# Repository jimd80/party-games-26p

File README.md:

# 26 Player party game setup

Up to 26 senders

go to a single receiver

Sending keys A–Z for 26 players.

## The concept
Up to 26 micro:bits act as wireless game controllers. One micro:bit is used as a receiver. Each time a player presses a button, the receiver micro:bit sends a character (A–Z) to the serial port of the Arduino. The Arduino acts as a virtual keyboard for the PC and passes the player's keystrokes as a–z keypresses (player 1 = a, player 2 = b, ..., player 26 = z).

This has some benefits:
- No drivers required; works on any PC, Mac, Chromebook, tablet, etc.
- Games can be developed without the hardware; just use the keyboard `a`–`z` keys to test!
- Easy to develop!

## Setup
Of course you'll need games to play. Check out [games-examples](games-examples/README.md) for a guide on how to write games or directly try the examples.

### The sender
For the sender you have 2 options:
- A micro:bit with a battery box
- Or build the [game controller](https://github.com/jimd80/pxt-coderdojo-controller)

Load [microbit-GameController-v25.12.hex](sender-microbit-src/microbit-GameController-v25.12.hex) from [sender-microbit-src](sender-microbit-src/README.md) into each sender micro:bit using [MakeCode](https://makecode.microbit.org/#editor) or drag it to the `MICROBIT` folder in your file manager.

### The receiver
Get an Arduino Micro, or the Pro Micro clone. Flash [receiver-arduino-v25.7.hex](receiver-arduino-src/release/receiver-arduino-v25.7.hex) from [receiver-arduino-src](receiver-arduino-src/README.md) into the Arduino.

Get a dedicated micro:bit to use as a receiver. Flash [microbit-GameReceiver-v26.3.hex](receiver-microbit-src/microbit-GameReceiver-v26.3.hex) from [receiver-microbit-src](receiver-microbit-src/README.md) into the receiver micro:bit.

Connect the Arduino and micro:bit with 3 wires, as described in [receiver-arduino-src](receiver-arduino-src/README.md).

Alternatively, build the receiver PCB as described in [receiver-pcb](receiver-pcb/README.md).

## How to play
There are plenty of modes to use this setup. We'll go from easy to advanced.

### Quick 26 player
The easiest and fastest setup to play a multiplayer game.

**Senders**: Players just need to turn on their micro:bit. A `?` will appear shortly and a letter is auto-assigned. Button A is the action key to play.

**Receiver**: Plug in the receiver. `26` will appear briefly on the screen. Press button B until `A` (**A**uto-assign) appears and press button A to confirm.

### Personalized 26 player
The controllers are personalized. Give each player a secret code they need to enter into their micro:bit in order for their predefined letter to appear. If managed well, games can keep a preset list of the players' names to show in-game names of the players. The list of "secret codes" can be found in [sender-microbit-src](sender-microbit-src/README.md).

**Senders**: After a player has powered up their micro:bit, a `?` will appear. Now they need to input their code by pressing A and B alternately. For example, if a code is 4567, then A needs to be pressed 4 times, B 5 times, A 6 times, and B 7 times. After this, their assigned letter will appear on the screen.

**Receiver**: Just plug in the receiver; the default mode will just work.

### Programming challenge 26 player
For an extended experience, you can let the players program their micro:bit by themselves with MakeCode blocks.

**Senders**: Let the players create the code as shown in [sender-microbit-src](sender-microbit-src/README.md) (replacing 9999 with their personal code).

**Receiver**: Just plug in the receiver; the default mode will just work.

### 8 button mode 26 player
Games can be advanced to enable all 8 buttons from each player's controller. In this mode, the game not only needs to look at the letter that was pressed, but also at the preceding number, which indicates the button. Each button press from a player is sent as 2 keystrokes, like `5c` = button 5 for player c. More information can be found in [games-examples](games-examples/README.md).

This mode only works if you have both the [game controller](https://github.com/jimd80/pxt-coderdojo-controller) and [receiver PCB](receiver-pcb/README.md).

**Senders**: Same setup as **Quick 26 player** or **Personalized 26 player**.

**Receiver**: Plug in the receiver. Long-press button 4 on the receiver PCB. The green LED will turn on to indicate multi-button mode.

### 8 button mode 4 player
Another way of enabling all 8 buttons per player is limiting the maximum player count to 4. In this way, all 32 keys (8 x 4) can be mapped to a single key on the keyboard, making game programming much easier than the 8-button 26-player mode above.

This mode only works if you have the [game controller](https://github.com/jimd80/pxt-coderdojo-controller).

**Senders**: Power on the micro:bit so `?` appears. Hold A+B until I, II, III, or IIII shows up on the screen to choose player 1–4.

**Receiver**: Plug in the receiver. Press button A until `4` shows up on the screen. The first row of 4 LEDs shows the online status of controllers 1–4.

### Micro:bit project mode
This mode is not to be used with the receiver, but with another custom-programmed micro:bit controlling their own hardware project. More info in the [Remote controlled car exercise](https://drive.google.com/file/d/1tmhRcf0qA-TUM9EA2VIr5EyiVHkkNPFD/view?usp=sharing) (in Dutch).

**Sender**: Power on the micro:bit so `?` appears. Hold A+B until 1, 2, 3, 4, 5, 6, 7, or 8 appears.

**Receiver**: This is a custom program controlling hardware with the game controller.

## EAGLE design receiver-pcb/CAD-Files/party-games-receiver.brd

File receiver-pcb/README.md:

## Hardware building guide
The (empty) PCB can be easily manufactured by any PCB company, for example JLCPCB which is known as the cheapest. The (tripod) holder can be 3D printed with any 3D printer, for example the affordable Creality Ender V2 or V3.

Other parts can be ordered at various electronics suppliers such as LCSC, AliExpress, DigiKey, Farnell, etc. The most difficult part to source will be the micro:bit EDGE connector. This needs to be the horizontal SMD version, and needs to look exactly like this:

Soldering can be done with (lead-free) solder paste and a reflow oven, or if you are a bit handy it can also be done with a classic soldering iron, lead-free solder wire, and some flux. In that case, it will be handy to have something to keep the parts in place while soldering, such as a screwdriver.

## Tools needed

You'll need some tools and skills to build this project:
- A soldering iron and lead-free solder wire
- Optionally, a reflow oven OR a hot-air gun. Using this option you'll also need lead-free solder paste, such as Chipquik TS391SNL
- Recommended: Flux, such as Chipquik SMD291NL

## Step 1: Ordering the parts
Collect these parts:

Part number      |Reference	            |Description                      |Qty|Price|Order link example|
:----------------|:---------------------|:--------------------------------|--:|----:|:-----------------|
R1, R2, R7, R8   |Res 470R SMD0805      |Resistor 470R / 1% / 0.1W / 0805 |  4|€0.02|[LCSC](https://www.lcsc.com/product-detail/Chip-Resistor-Surface-Mount_YAGEO-RC0805FR-07470RL_C114564.html)|
R3, R4, R5, R6   |Res 10K SMD0805       |Resistor 10K / 1% / 0.1W / 0805  |  4|€0.06||
C1               |Cap 100nF SMD0805     |Capacitor 100nF / 50V / SMD 0805 |  1|€0.04||
SW1,2,3,4        |Pushbutton 6x6x5mm    |Pushbutton (on)-off 6x6x5mm      |  4|€0.05|[AliExpress](https://www.aliexpress.com/item/1005001897291190.html)|
J1, J2           |Pinhdr 1x17           |Pinheader 17p 2.54mm             |  2|€0.04||
J3               |Edge connector hor SMD|Micro:bit edge connector SMD/hor |  1|€0.85|[AliExpress](https://www.aliexpress.com/item/1005006206948907.html)|
J4, J5           |Pinhdr 1x12           |Pinheader 12p 2.54mm             |  2|€0.04||
LD1              |LED Green SMD0805     |Led Green SMD 0805               |  1|€0.02|[LCSC](https://www.lcsc.com/product-detail/LED-Indication-Discrete_XINGLIGHT-XL-2012UGC_C965815.html)|
LD2              |LED Red SMD0805       |Led Red SMD 0805                 |  1|€0.02|[LCSC](https://www.lcsc.com/product-detail/LED-Indication-Discrete_XINGLIGHT-XL-2012SURC_C965812.html)|
Other            |Screw M3x10           |Screw M3x10 flat head            |  3|€0.04||
Other            |1/4-20 UNC nut        |Tripod mounting insert nut       |  2|€0.10|[AliExpress](https://nl.aliexpress.com/item/1005008462611857.html)|

## Step 2: Ordering the PCB
The PCB (without components) needs to be manufactured by a company. Here are the instructions for JLCPCB:
- Create a zip file from the `Gerber-JLCPCB` folder
- Go to https://jlcpcb.com
- Choose "Add Gerber file" and upload the zip file you created
- Select your desired quantity (the more you order, the cheaper per board)
- Change PCB Color to Black
- Change Surface Finish to LeadFree HASL (if RoHS is required in your country; this is always the case for the EU)
- Choose Mark on PCB: Remove Mark  
All other options are okay by default. Complete the order process.

## Step 3: Solder the edge connector
The edge connector is preferably soldered with a soldering iron, as it is not clear if it can withstand the 240 °C hot air required for lead-free soldering. Use extra flux to create smooth joints. After soldering, remove the flux with isopropyl alcohol.

## Step 4: Solder the SMD parts
In the bill of materials above you'll find which parts belong to which part numbers printed on the PCB (such as R1, C1, ...). Only for the two LEDs does the direction of the part (polarity) matter. There is usually an indicator (like a small green dot or a line) that should point in the direction of the arrow on the PCB.

Soldering SMD parts can be done in several ways; there are many tutorials online such as https://www.youtube.com/watch?v=hoLf8gvvXXU or https://www.youtube.com/watch?v=fYInlAmPnGo.

## Step 5: Solder the pin headers and Arduino / Pro Micro
When using an Arduino Micro, solder the J1 and J2 pin headers onto the PCB. Next, place the Arduino (with the USB connector pointing to the left) over the pin headers and solder it.

When using a Pro Micro, solder J4 and J5 instead.

## Step 6: Program the Arduino / Pro Micro

Flash the hex file found in `receiver-arduino-src/release` to the Arduino / Pro Micro (using Arduino IDE or VS Code with PlatformIO).

Check if it works by unplugging and plugging the Arduino back in. Open Notepad and press button 1; an `a` (or `q`) keypress should be registered on each press.

## Step 7: 3D print the holder
This step is not required if you just want to put the PCB on a table during use:
- Download [party-games-receiver.stl](CAD-Files/party-games-receiver.stl)
- Process the file in your slicer. Recommended layer height is 0.2 mm and recommended speed is 50 mm/s.
- Print it, preferably with black PETG, as this is more fire-resistant than PLA or ABS.
- Use a soldering iron to hot-press-insert the tripod mounting nuts into the holder.

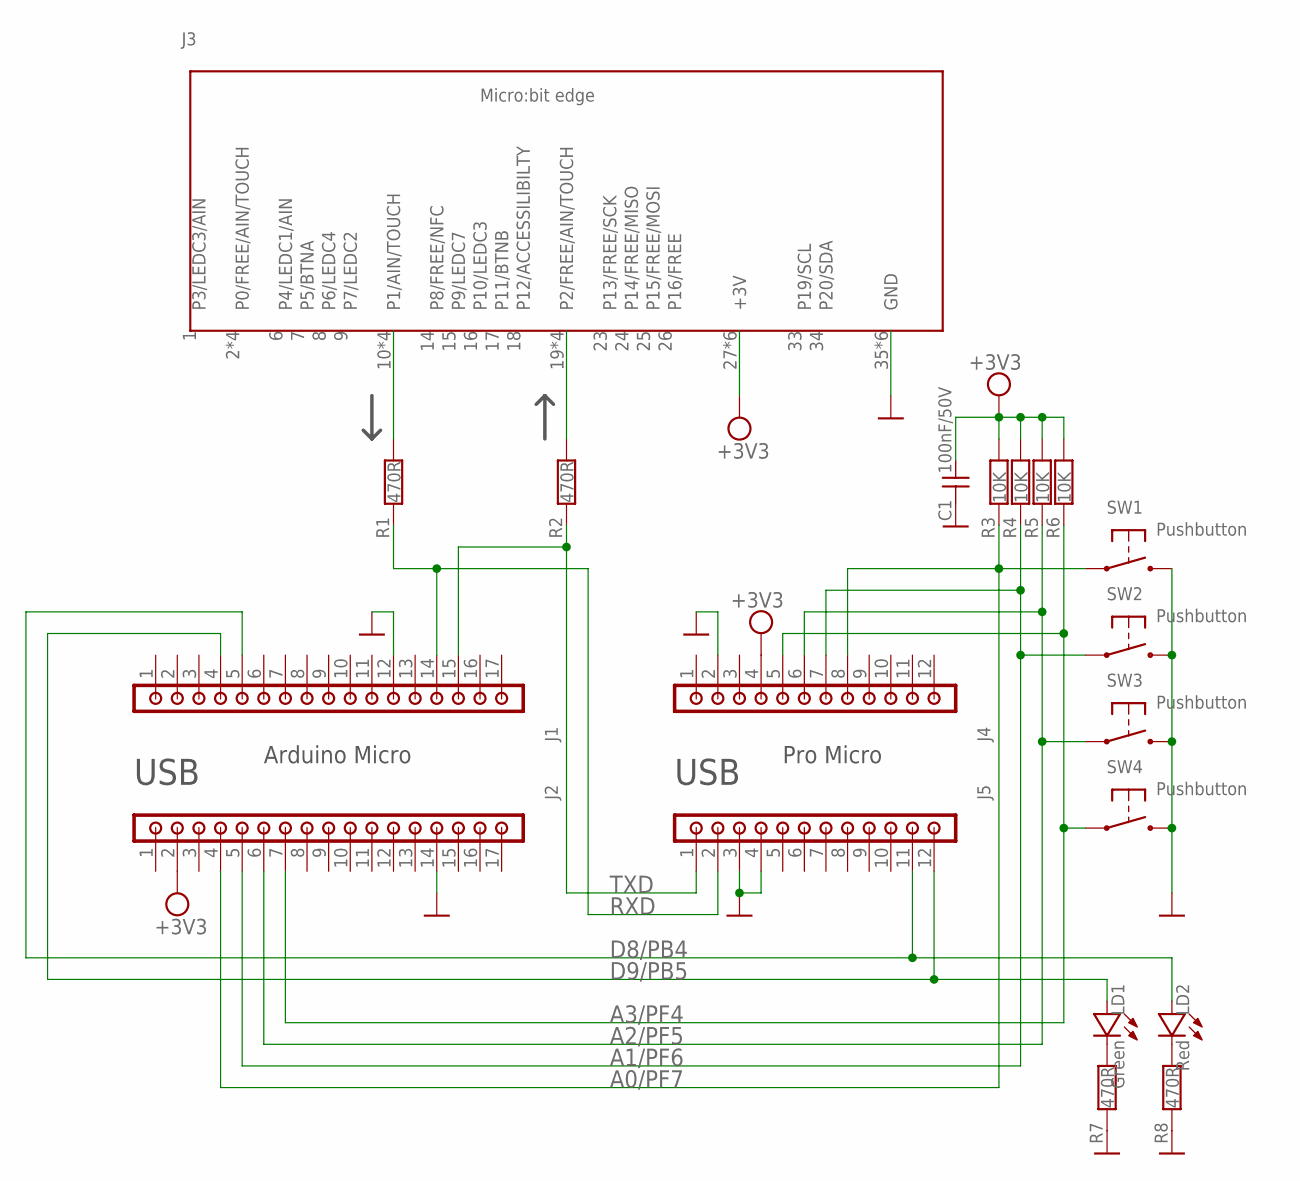
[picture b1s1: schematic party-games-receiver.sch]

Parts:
C1: CC100NA; CAP_0805
J1, J2: CJHDR1X17MA; CON_HDR_M_1X17
J3: CJMBITH; SOCKET_MBIT_H
J4, J5: CJHDR1X12MA; CON_HDR_M_1X12
LD1: CDLEDGNC; LED_0805
LD2: CDLEDRDC; LED_0805
R1, R2, R7, R8: CR470RA; RES_0805
R3, R4, R5, R6: CR10KA; RES_0805
SW1, SW2, SW3, SW4: CSWPUSHA; SWITCH_PUSH_5MM

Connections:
+3V3: C1.2, J2.2, J3.27 (+3V), J3.28 (+3V), J3.29 (+3V), J3.30 (+3V), J3.31 (+3V), J3.32 (+3V), J4.4, R3.2, R4.2, R5.2, R6.2
A0/PF7: J2.4, J4.8, R3.1, SW1.3, SW1.4
A1/PF6: J2.5, J4.7, R4.1, SW2.3, SW2.4
A2/PF5: J2.6, J4.6, R5.1, SW3.3, SW3.4
A3/PF4: J2.7, J4.5, R6.1, SW4.3, SW4.4
D8/PB4: J1.5, J5.11, LD2.A
D9/PB5: J1.4, J5.12, LD1.A
GND: C1.1, J1.12, J2.14, J3.35 (GND), J3.36 (GND), J3.37 (GND), J3.38 (GND), J3.39 (GND), J3.40 (GND), J4.2, J5.3, J5.4, R7.1, R8.1, SW1.1 (S), SW1.2 (S), SW2.1 (S), SW2.2 (S), SW3.1 (S), SW3.2 (S), SW4.1 (S), SW4.2 (S)
unnamed: LD1.C, R7.2
unnamed: J3.10 (P1/AIN/TOUCH), J3.11 (P1/AIN/TOUCH), J3.12 (P1/AIN/TOUCH), J3.13 (P1/AIN/TOUCH), R1.2
unnamed: J3.19 (P2/FREE/AIN/TOUCH), J3.20 (P2/FREE/AIN/TOUCH), J3.21 (P2/FREE/AIN/TOUCH), J3.22 (P2/FREE/AIN/TOUCH), R2.2
unnamed: LD2.C, R8.2
RXD: J1.14, J5.2, R1.1
TXD: J1.15, J5.1, R2.1

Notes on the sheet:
USB
Arduino Micro
Pro Micro

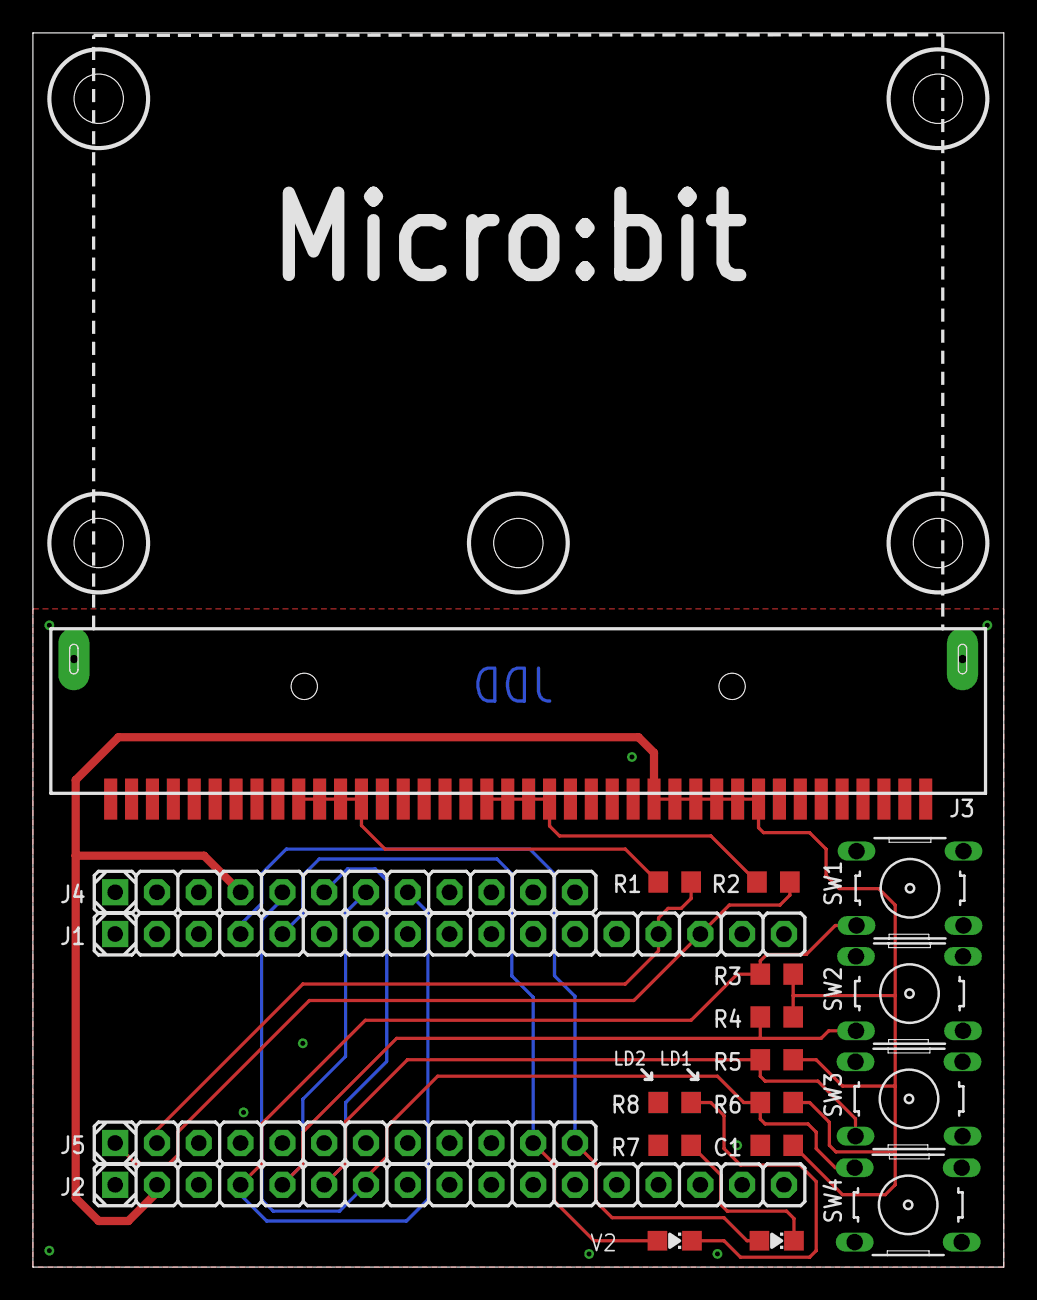
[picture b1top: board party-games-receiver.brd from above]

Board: 2 copper layers, 59.0 x 75.0 mm, 25 parts (0 on the bottom side), 14 nets.

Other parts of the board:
U$5, U$6, U$7, U$8, U$9: HOLE_3MM_ISOLATED

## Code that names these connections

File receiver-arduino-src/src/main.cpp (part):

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#define KEY_UP_PREFIX '\x0F'

// LED's and buttons on interface circuit board
#define LED_RED 8   // atmel PB4  Indicates when paused (supress keystrokes)
#define LED_GREEN 9 // atmel PB5  Show receiving data
#define BUTTON1 18  // atmel PF7  Send single char 'a' to keyboard (to test qwerty / azerty)
#define BUTTON2 19  // atmel PF6  Send 30 keys/sec a..z (2x each)
#define BUTTON3 20  // atmel PF5  Send 300 keys/sec a..z (20x each)
#define BUTTON4 21  // atmel PF4  Pause / Resume

// Includes
#include <Arduino.h>
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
